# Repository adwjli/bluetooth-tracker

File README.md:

# Bluetooth Tracker

## Introduction
A Bluetooth Tracker inspired by the Tile Mate Bluetooth Tracker, built around the Nordic nRF51822 Bluetooth transceiver. The device can be programmed to pair with any Android or iOS mobile device via a mobile app.

The design of the trace antenna was provided by Texas Instrument in Application Note AN043. It is an Inverted F Antenna (IFA) with a matched 50 Ohm characteristic impedance at 2.4GHz. The device is capable of up to 4dBm of transmit power.

## Gallery

## Copper Layers

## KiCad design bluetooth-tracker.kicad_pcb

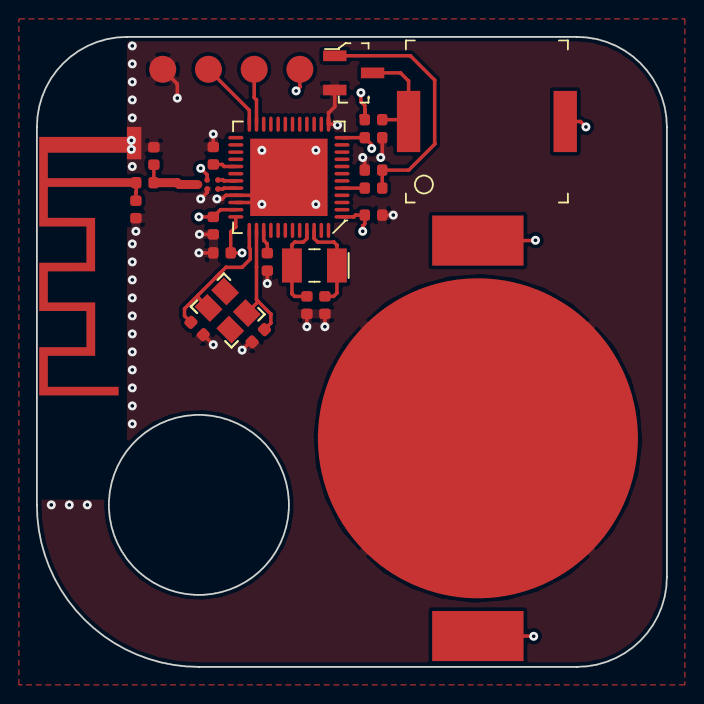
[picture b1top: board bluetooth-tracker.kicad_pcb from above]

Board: 4 copper layers, 35.0 x 35.0 mm, 25 parts (0 on the bottom side), 17 nets.

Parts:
AE1: ANTENNA-IFA-2.4GHZ; ANTENNA-IFA-2.4GHZ-2
BAT1: CR2032_CLIP2
BZ1: PKMCS0909E4000-R1; Piezo_9x9mm_PKLCS1212E40A1-R1
C1, C3: 22pF; C_0402_1005Metric
C2, C4: 15pF; C_0402_1005Metric
C5, C6: 1nF; C_0402_1005Metric
C7, C8, C15: 100nF; C_0402_1005Metric
C10: 47nF; C_0402_1005Metric
C13: 1.0pF; C_0402_1005Metric
C14: 1.5pF; C_0402_1005Metric
GN1: BAL-NRF01D3; FCBGA-5N
J1: CONN4PROG
L3: 3.3nH; L_0402_1005Metric
Q1: FDV301N_G; SOT-23-3_G
R1, R3: 1k; R_0402_1005Metric
R2: 100k; R_0402_1005Metric
U1: NRF51822-QFAA-T_G; QFN-48-1EP_6x6mmG
XTAL1: ECS-_327-12_5-34B-TR; SMD-2_3.2x1.5mmG
XTAL2: NX2520SA-16MHZ-STD-CSW-5; SOIC254P1016X440-4N

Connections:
/ANT1: GN1.3C, U1.31
/ANT2: GN1.3A, U1.32
/DEC1: C7.1, U1.39
/DEC2: C10.1, U1.29
/PIEZO_DRIVE: R1.2, U1.5
/SWDCLK: J1.3, U1.24
/SWDIO: J1.2, U1.23
/XTAL_16MHZ_1: C2.1, U1.37, XTAL2.1
/XTAL_16MHZ_2: C4.1, U1.38, XTAL2.2
/XTAL_32KHZ_1: C1.1, U1.46, XTAL1.1
/XTAL_32KHZ_2: C3.1, U1.45, XTAL1.2
GND: AE1.2, BAT1.2, C1.2, C2.2, C3.2, C4.2, C5.2, C6.2, C7.2, C8.2, C10.2, C13.2, C14.2, C15.2, GN1.2A, J1.4, Q1.2, R2.2, U1.13, U1.33, U1.34, U1.49
unnamed: AE1.1, C14.1, L3.2
unnamed: BZ1.2, Q1.3, R3.1
unnamed: C13.1, GN1.1B, L3.1
unnamed: Q1.1, R1.1, R2.1
VCC: BAT1.1, BZ1.1, C5.1, C6.1, C8.1, C15.1, GN1.2C, J1.1, R3.2, U1.1, U1.12, U1.35, U1.36

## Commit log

2020-05-15 First commit.
2020-05-20 Commiting finished design files.
2020-05-20 Testing whether I can embedded PDFs in the README markdown.
2020-05-20 Replotted Gerbers, updated PCB design so that origin is at the hole.
2020-05-20 Added an image of the copper layers.
2020-05-21 Updating the README.md file. Testing markdown.
2020-05-21 Updating README.md.
2020-05-22 Updating README.md. Removing the redundant eqquations.
2020-05-22 Addin scene5.jpg.
2020-05-22 Adding fabrication drawing jpg.
2020-05-22 Adding assembly jpg.
2020-05-22 Updating README.md in assembly folder.
2020-05-22 Adding schematics drawing.
2020-05-22 Fixing typo in sch dwg.
2020-05-22 Updating the image of the PCB layers in README.md.
2020-05-22 Updating README.md
2020-05-25 Adding pick and place files, and new raster images.
